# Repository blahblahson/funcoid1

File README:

# FUNCOID1 - a 65C02 computer

This repository contains the FUNCOID1 design files for KiCad 5.

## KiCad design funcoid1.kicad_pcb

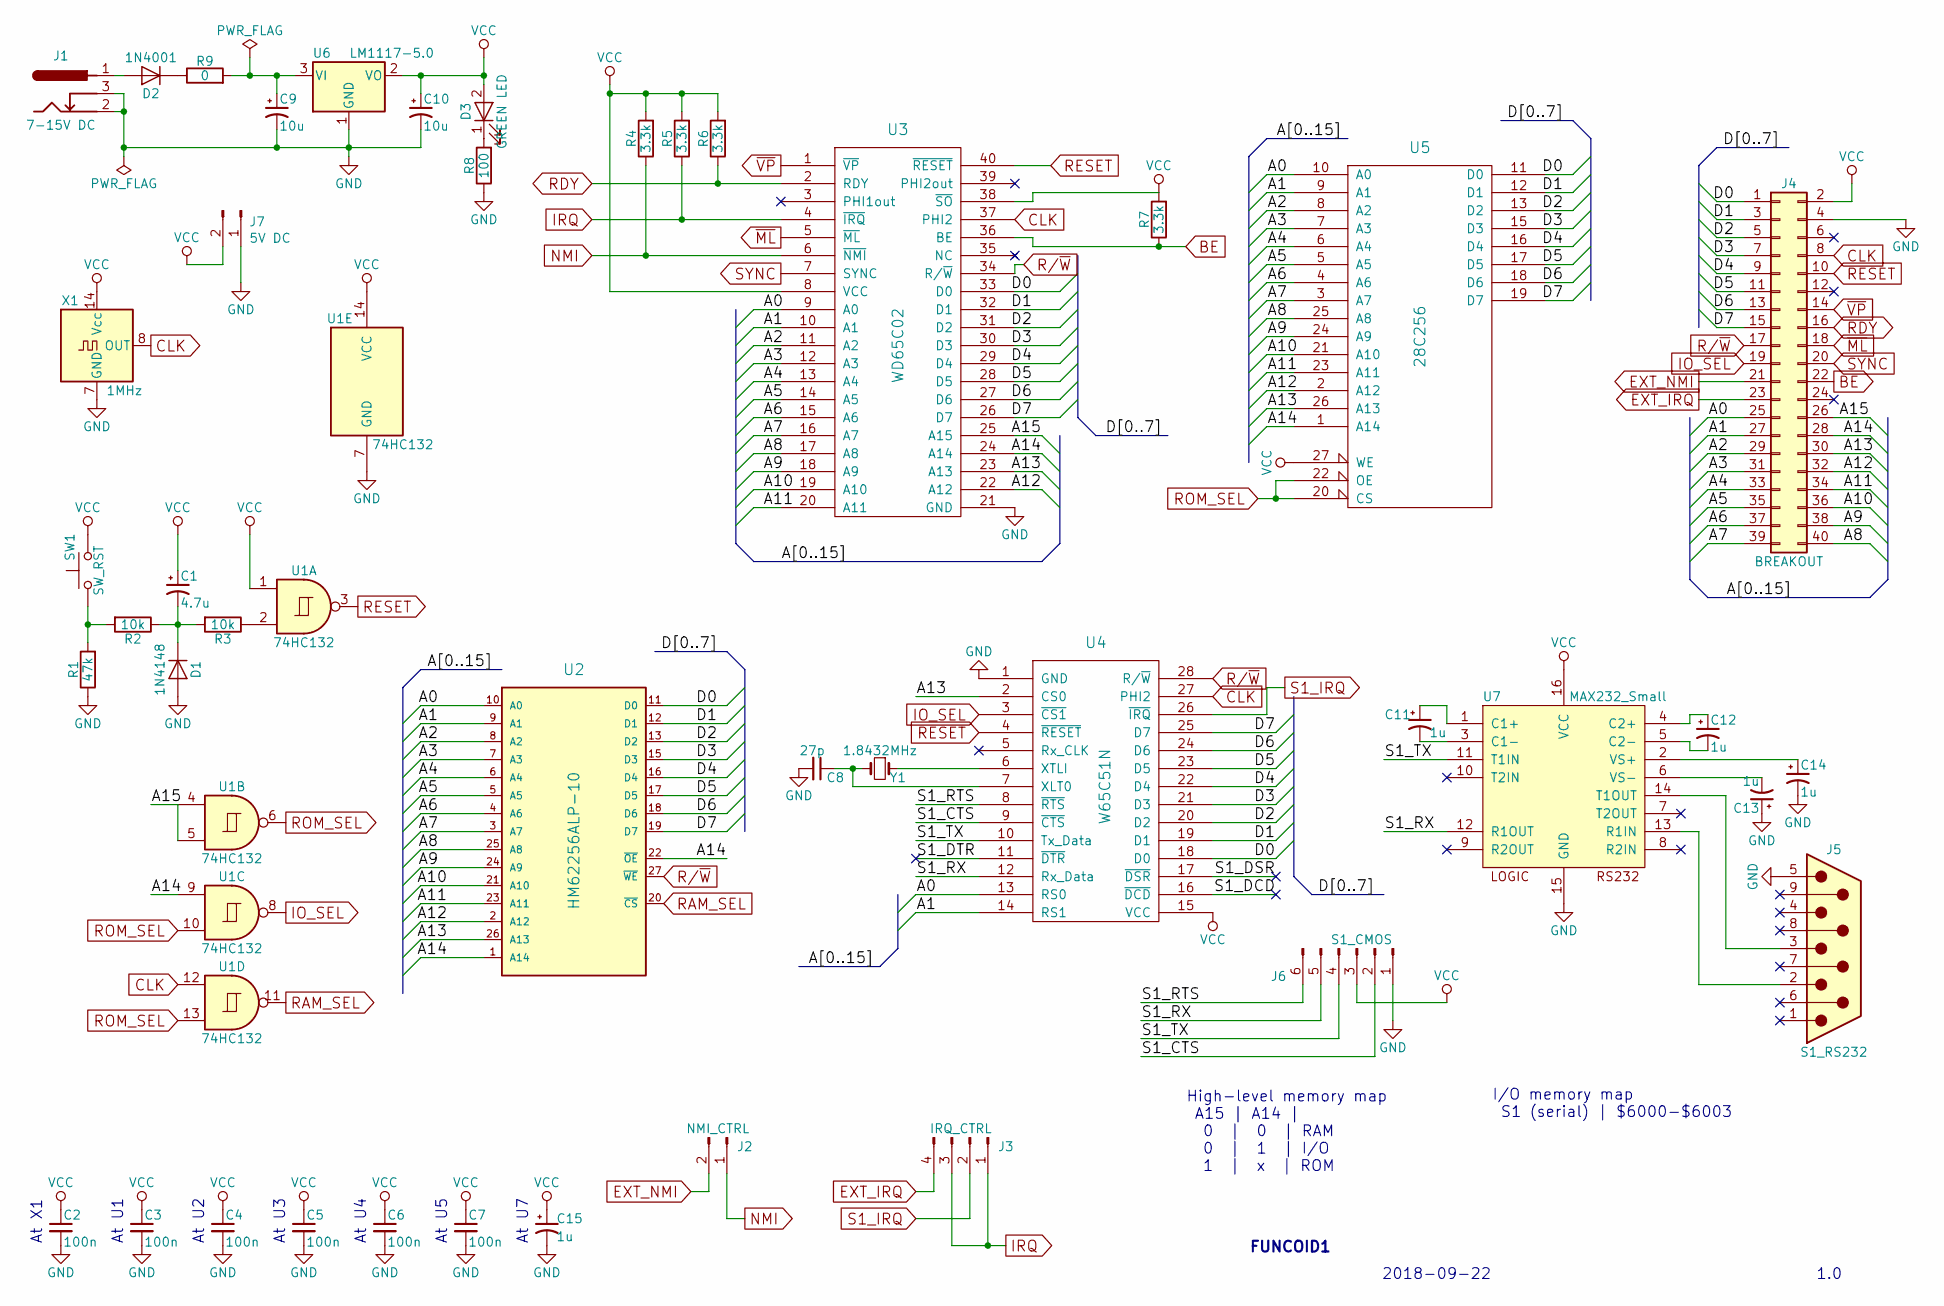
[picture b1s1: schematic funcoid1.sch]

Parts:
C1: 4.7u; CP_Radial_D5.0mm_P2.50mm
C2, C3, C4, C5, C6, C7: 100n; C_Disc_D5.0mm_W2.5mm_P5.00mm
C8: 27p; C_Disc_D5.0mm_W2.5mm_P5.00mm
C9, C10: 10u; C_Disc_D5.0mm_W2.5mm_P5.00mm
C11, C12, C13, C14, C15: 1u; C_Disc_D5.0mm_W2.5mm_P5.00mm
D1: 1N4148; D_DO-35_SOD27_P7.62mm_Horizontal
D2: 1N4001; D_DO-41_SOD81_P7.62mm_Horizontal
D3: GREEN LED; LED_D3.0mm
J1: 7-15V DC; BARREL_JACK
J2: NMI_CTRL; Pin_Header_Straight_1x02_Pitch2.54mm
J3: IRQ_CTRL; Pin_Header_Straight_1x04_Pitch2.54mm
J4: BREAKOUT; IDC-Header_2x20_Pitch2.54mm_Straight
J5: S1_RS232; DSUB-9_Female_Horizontal_Pitch2.77x2.84mm_EdgePinOffset7.70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
J6: S1_CMOS; PinHeader_1x06_P2.54mm_Horizontal
J7: 5V DC; PinHeader_1x02_P2.54mm_Vertical
R1: 47k; R_Axial_DIN0207_L6.3mm_D2.5mm_P7.62mm_Horizontal
R2, R3: 10k; R_Axial_DIN0207_L6.3mm_D2.5mm_P7.62mm_Horizontal
R4, R5, R6, R7: 3.3k; R_Axial_DIN0207_L6.3mm_D2.5mm_P7.62mm_Horizontal
R8: 100; R_Axial_DIN0207_L6.3mm_D2.5mm_P7.62mm_Horizontal
R9: 0; R_Axial_DIN0207_L6.3mm_D2.5mm_P7.62mm_Horizontal
SW1: SW_RST; SW_PUSH_6mm
U1: 74HC132; DIP-14_W7.62mm
U2: HM62256ALP-10; DIP-28_W15.24mm
U3: WD65C02; DIP-40_W15.24mm
U4: W65C51N; DIP-28_W15.24mm
U5: 28C256; DIP-28_W15.24mm
U6: LM1117-5.0; TO-220
U7: MAX232_Small; DIP-16_W7.62mm_Socket
X1: 1MHz; Oscillator_DIP-14
Y1: 1.8432MHz; Crystal_HC49-U_Vertical

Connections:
/A0: J4.25, U2.10 (A0), U3.9 (A0), U4.13 (RS0), U5.10 (A0)
/A1: J4.27, U2.9 (A1), U3.10 (A1), U4.14 (RS1), U5.9 (A1)
/A2: J4.29, U2.8 (A2), U3.11 (A2), U5.8 (A2)
/A3: J4.31, U2.7 (A3), U3.12 (A3), U5.7 (A3)
/A4: J4.33, U2.6 (A4), U3.13 (A4), U5.6 (A4)
/A5: J4.35, U2.5 (A5), U3.14 (A5), U5.5 (A5)
/A6: J4.37, U2.4 (A6), U3.15 (A6), U5.4 (A6)
/A7: J4.39, U2.3 (A7), U3.16 (A7), U5.3 (A7)
/A8: J4.40, U2.25 (A8), U3.17 (A8), U5.25 (A8)
/A9: J4.38, U2.24 (A9), U3.18 (A9), U5.24 (A9)
/A10: J4.36, U2.21 (A10), U3.19 (A10), U5.21 (A10)
/A11: J4.34, U2.23 (A11), U3.20 (A11), U5.23 (A11)
/A12: J4.32, U2.2 (A12), U3.22 (A12), U5.2 (A12)
/A13: J4.30, U2.26 (A13), U3.23 (A13), U4.2 (CS0), U5.26 (A13)
/A14: J4.28, U1.9, U2.1 (A14), U2.22 (~OE), U3.24 (A14), U5.1 (A14)
/A15: J4.26, U1.4, U1.5, U3.25 (A15)
/D0: J4.1, U2.11 (D0), U3.33 (D0), U4.18 (D0), U5.11 (D0)
/D1: J4.3, U2.12 (D1), U3.32 (D1), U4.19 (D1), U5.12 (D1)
/D2: J4.5, U2.13 (D2), U3.31 (D2), U4.20 (D2), U5.13 (D2)
/D3: J4.7, U2.15 (D3), U3.30 (D3), U4.21 (D3), U5.15 (D3)
/D4: J4.9, U2.16 (D4), U3.29 (D4), U4.22 (D4), U5.16 (D4)
/D5: J4.11, U2.17 (D5), U3.28 (D5), U4.23 (D5), U5.17 (D5)
/D6: J4.13, U2.18 (D6), U3.27 (D6), U4.24 (D6), U5.18 (D6)
/D7: J4.15, U2.19 (D7), U3.26 (D7), U4.25 (D7), U5.19 (D7)
/S1_CTS: J6.2, U4.9 (~CTS)
/S1_DCD: U4.16 (~DCD)
/S1_DSR: U4.17 (~DSR)
/S1_DTR: U4.11 (~DTR)
/S1_RTS: J6.6, U4.8 (~RTS)
/S1_RX: J6.5, U4.12 (Rx_Data), U7.12 (R1OUT)
/S1_TX: J6.4, U4.10 (Tx_Data), U7.11 (T1IN)
BE: J4.22, R7.1, U3.36 (BE)
CLK: J4.8, U1.12, U3.37 (PHI2), U4.27 (PHI2), X1.8 (OUT)
EXT_IRQ: J3.4, J4.23
EXT_NMI: J2.2, J4.21
GND: C2.2, C3.2, C4.2, C5.2, C6.2, C7.2, C8.2, C9.2, C10.2, C13.1, C14.2, C15.2, D1.2 (A), J1.2, J1.3, J4.4, J5.5, J6.1, J7.1, R1.1, R8.1, U1.7 (GND), U2.14 (GND), U3.21 (GND), U4.1 (GND), U5.14 (GND), U6.1 (GND), U7.15 (GND), X1.7 (GND)
IO_SEL: J4.19, U1.8, U4.3 (~CS1)
IRQ: J3.1, J3.3, R5.1, U3.4 (~IRQ)
NMI: J2.1, R4.1, U3.6 (~NMI)
unnamed: C1.2, D1.1 (K), R2.1, R3.2
unnamed: C8.1, U4.7 (XLT0), Y1.2
unnamed: C9.1, R9.2, U6.3 (VI)
unnamed: C11.1, U7.1 (C1+)
unnamed: C11.2, U7.3 (C1-)
unnamed: C12.1, U7.4 (C2+)
unnamed: C12.2, U7.5 (C2-)
unnamed: C13.2, U7.6 (VS-)
unnamed: C14.1, U7.2 (VS+)
unnamed: D2.1 (K), R9.1
unnamed: D2.2 (A), J1.1
unnamed: D3.1 (K), R8.2
unnamed: J5.2, U7.13 (R1IN)
unnamed: J5.3, U7.14 (T1OUT)
unnamed: R1.2, R2.2, SW1.1
unnamed: R3.1, U1.2
unnamed: U4.6 (XTLI), Y1.1
R/~W: J4.17, U2.27 (~WE), U3.34 (R/~W), U4.28 (R/~W)
RAM_SEL: U1.11, U2.20 (~CS)
RDY: J4.16, R6.1, U3.2 (RDY)
RESET: J4.10, U1.3, U3.40 (~RESET), U4.4 (~RESET)
ROM_SEL: U1.6, U1.10, U1.13, U5.20 (CS), U5.22 (OE)
S1_IRQ: J3.2, U4.26 (~IRQ)
SYNC: J4.20, U3.7 (SYNC)
VCC: C1.1, C2.1, C3.1, C4.1, C5.1, C6.1, C7.1, C10.1, C15.1, D3.2 (A), J4.2, J6.3, J7.2, R4.2, R5.2, R6.2, R7.2, SW1.2, U1.1, U1.14 (VCC), U2.28 (VCC), U3.8 (VCC), U3.38 (~SO), U4.15 (VCC), U5.27 (WE), U5.28 (VCC), U6.2 (VO), U7.16 (VCC), X1.14 (Vcc)
~ML: J4.18, U3.5 (~ML)
~VP: J4.14, U3.1 (~VP)

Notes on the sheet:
At X1
At U1
At U2
At U3
At U4
At U5
High-level memory map A15 | A14 | 0 | 0 | RAM 0 | 1 | I/O 1 | x | ROM
FUNCOID1
2018-09-22
1.0
I/O memory map S1 (serial) | $6000-$6003
At U7

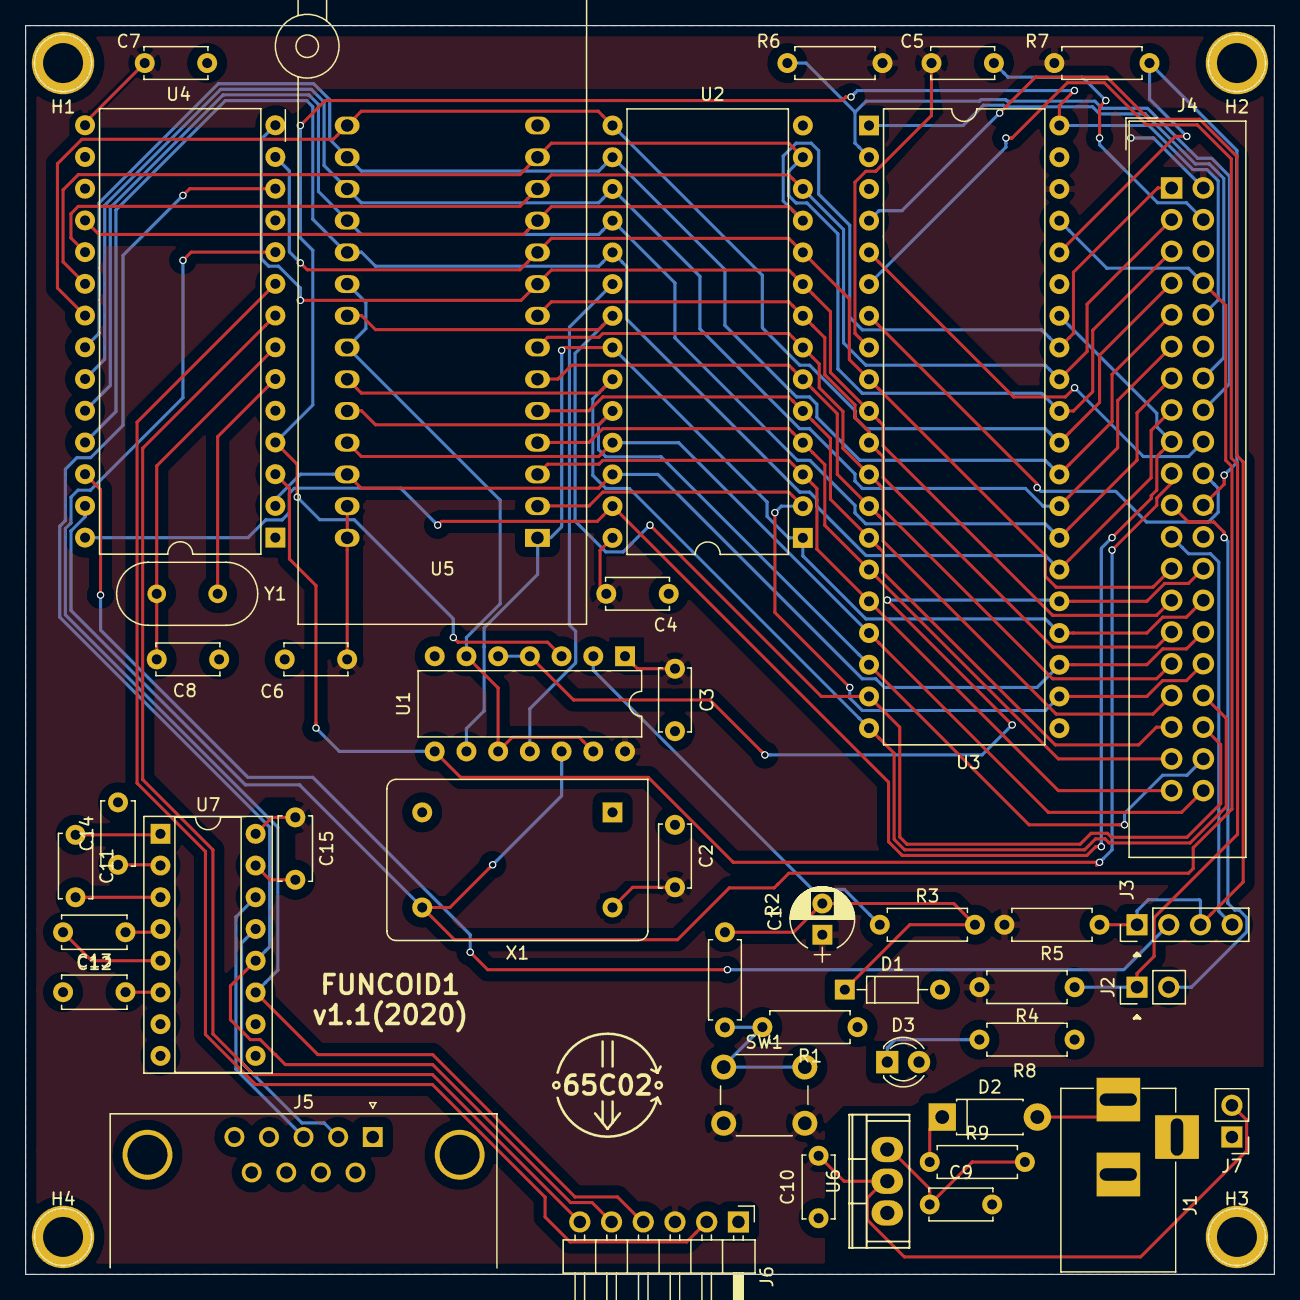
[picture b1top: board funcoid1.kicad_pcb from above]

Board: 2 copper layers, 100.0 x 100.0 mm, 48 parts (0 on the bottom side), 63 nets.

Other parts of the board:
H1, H2, H3, H4: mounthole

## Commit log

2019-05-17 FUNCOID1 first spin
    The schematic and PCB layout that correspond to the first spin of
    FUNCOID1. Gerber files were generated from this project and sent to
    DirtyPCBs (2018-09-22).
2019-10-13 Add additional KiCad lint to .gitignore
2019-10-15 Update to KiCad 5
    Not sure if all the right files are here. Fingers crossed.
2019-10-15 Use a ZIF footprint for U5 (EEPROM)
    ZIF sockets have feet that are slightly too wide to fit in a regular DIP
    footprint's drill holes. This caused me issues in the fist spin of
    FUNCOID1. Replace it with a ZIF footprint as was originally envisaged.
    I had to upgrade to KiCad 5 to make use of these new footprints. I made
    a custom derivative where the ZIF lever is facing the other way, but
    preserving the orientation of the pads.
2020-03-21 Add a MAX232 for proper RS-232 signalling
    Use a MAX232 to drive the signal on the DB9 connector, such that it is
    RS-232 compliant and will be understood by my VT510 terminal. Route the
    old 5V CMOS UART to a new 6-pin header for use with an FTDI.
    This change also moves the DB9 connector to the same edge as the barrel
    jack, which should make designing a box a little easier.
    Finally, do some general re-routing on the PCB layout.
